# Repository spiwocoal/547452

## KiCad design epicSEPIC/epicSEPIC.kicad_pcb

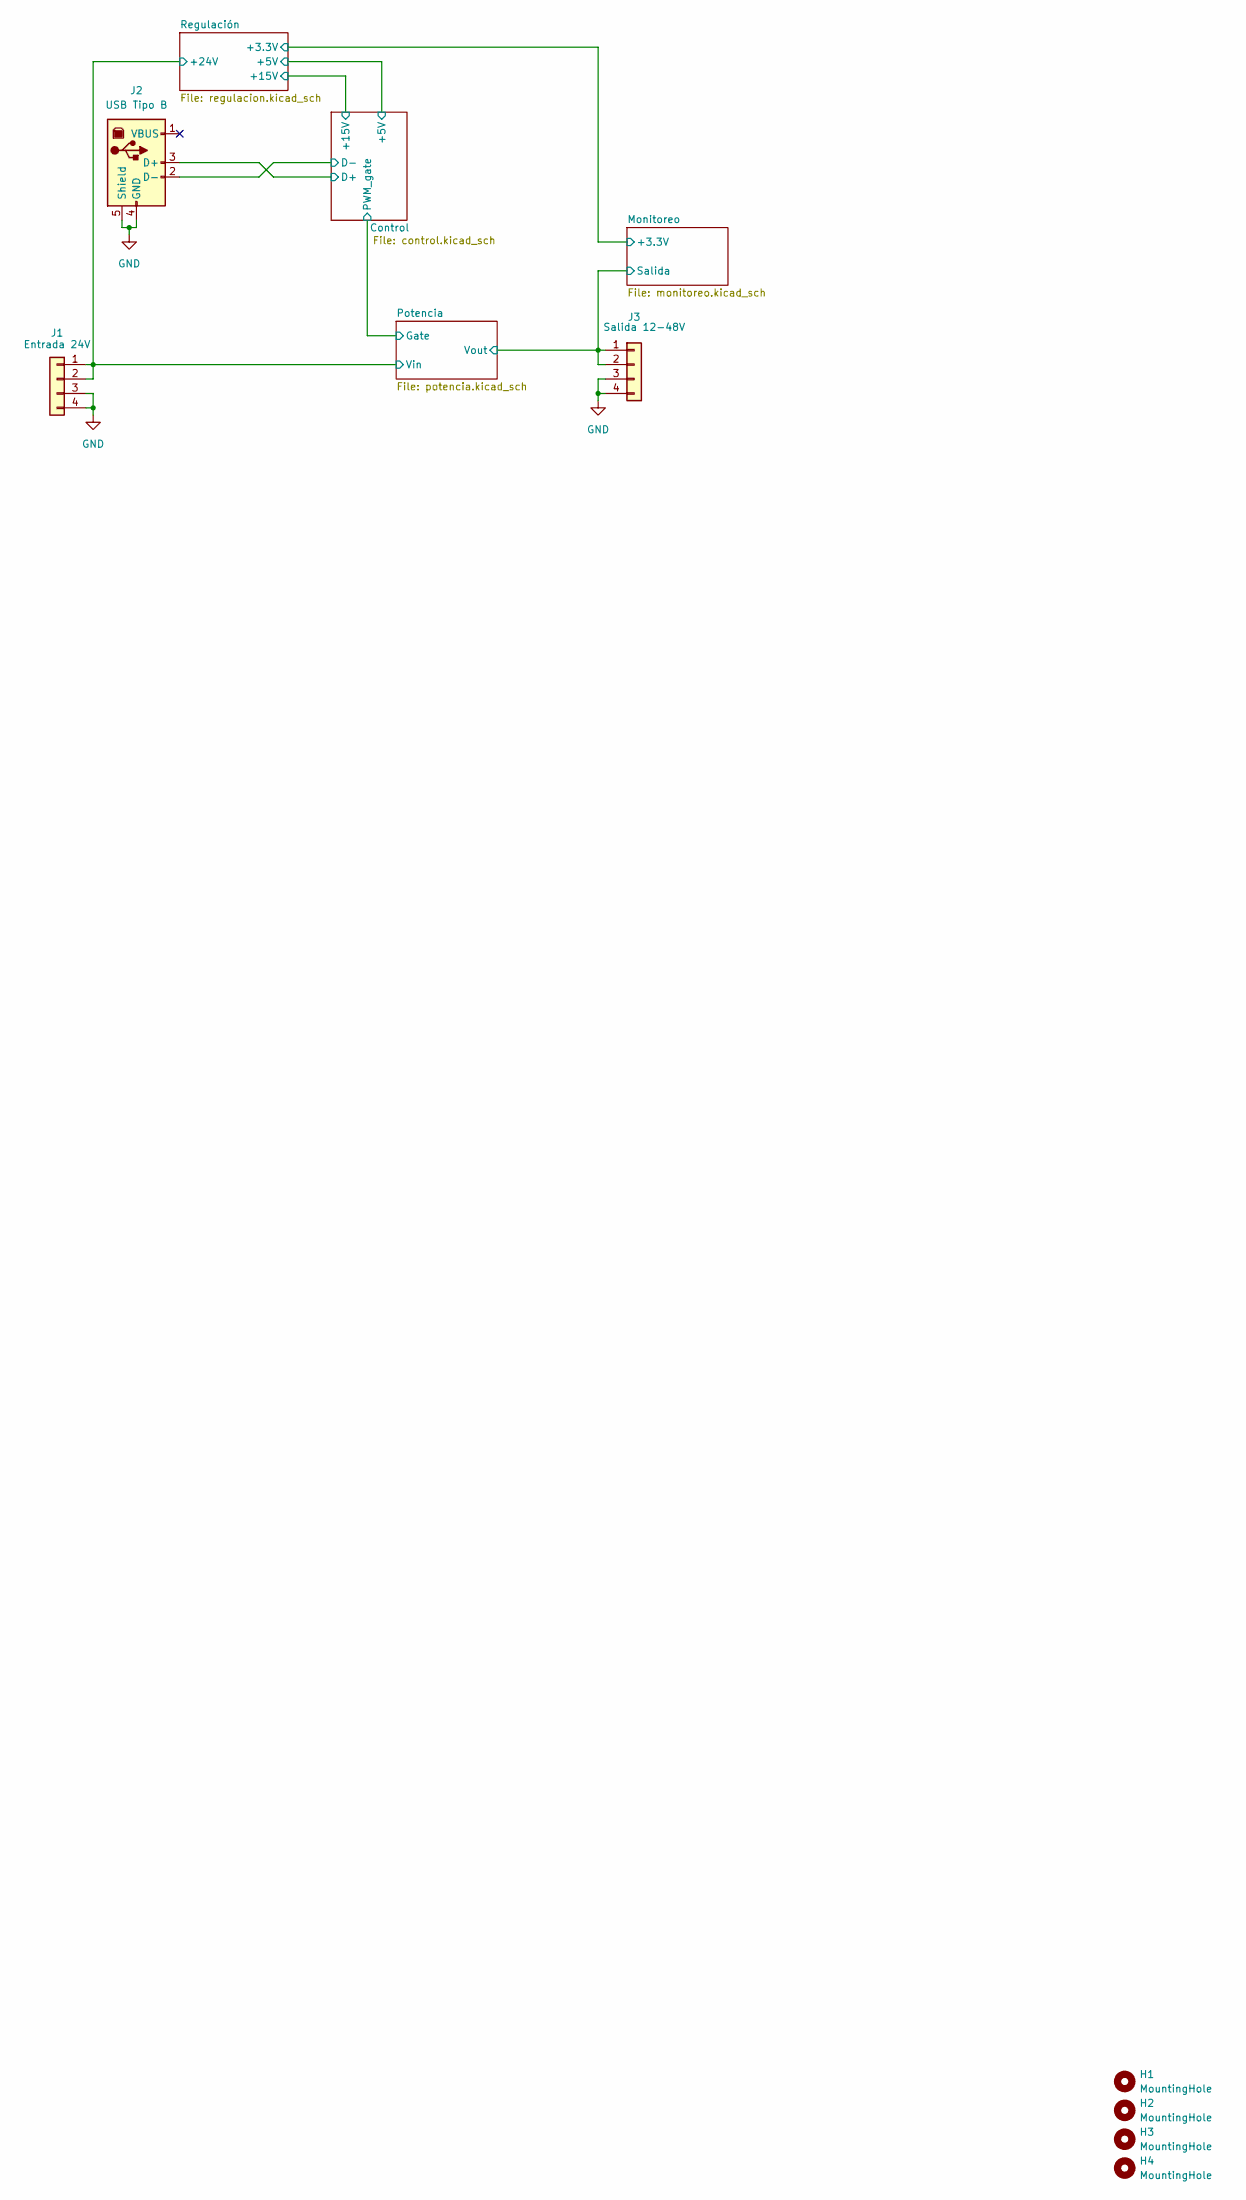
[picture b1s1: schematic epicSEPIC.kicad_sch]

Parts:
H1, H2, H3, H4: MountingHole; MountingHole_3.2mm_M3_ISO14580
J1: Entrada 24V; 1822752; MfgPN 1823638
J2: USB Tipo B; USB_B_Lumberg_2411_02_Horizontal; MfgPN 61729-0010RLF
J3: Salida 12-48V; 1822752; MfgPN 1823638

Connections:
/Control/D+: J2.3 (D+); also elsewhere on the board
/Control/D-: J2.2 (D-); also elsewhere on the board
/Monitoreo/Salida: J3.1, J3.2; also elsewhere on the board
/Potencia/Vin: J1.1, J1.2; also elsewhere on the board
GND: J1.3, J1.4, J2.4 (GND), J2.5 (Shield), J3.3, J3.4; also elsewhere on the board

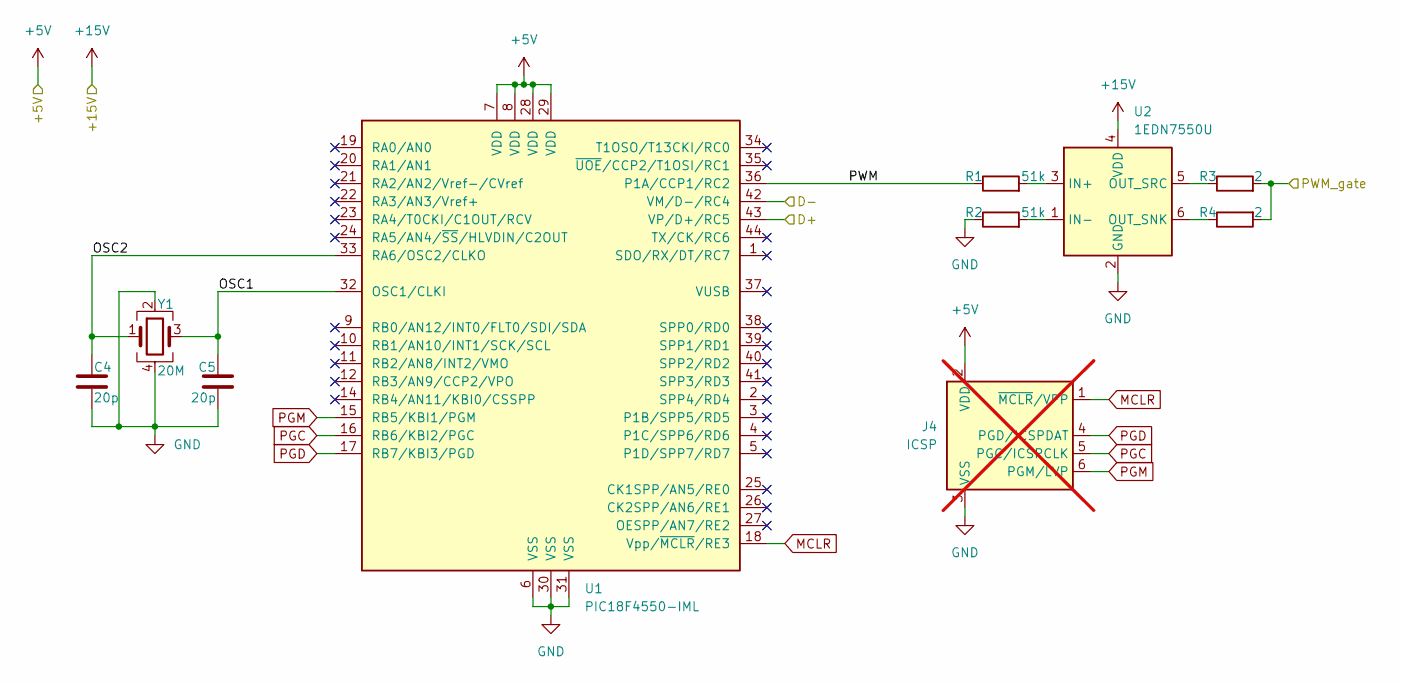
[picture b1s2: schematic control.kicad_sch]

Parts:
C4, C5: 20p; C_0402_1005Metric; MfgPN C0402C200M8HACTU
J4: ICSP; PinSocket_1x06_P1.00mm_Vertical; not fitted
R1, R2: 51k; R_0603_1608Metric; MfgPN ESR03EZPD5102
R3, R4: 2; R_0402_1005Metric; MfgPN RT0402BRE072RL
U1: PIC18F4550-IML; QFN-44-1EP_8x8mm_P0.65mm_EP6.45x6.45mm; MfgPN PIC18F4550-IML
U2: 1EDN7550U; PG-TSNP-6-13; MfgPN 1EDN7550U
Y1: 20M; Crystal_SMD_2520-4Pin_2.5x2.0mm; MfgPN FH2000021

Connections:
+5V: J4.2 (VDD), U1.7 (VDD), U1.8 (VDD), U1.28 (VDD), U1.29 (VDD); also elsewhere on the board
+15V: U2.4 (VDD); also elsewhere on the board
/Control/D+: U1.43 (VP/D+/RC5); also elsewhere on the board
/Control/D-: U1.42 (VM/D-/RC4); also elsewhere on the board
/Control/OSC1: C5.2, U1.32 (OSC1/CLKI), Y1.3
/Control/OSC2: C4.1, U1.33 (RA6/OSC2/CLKO), Y1.1
/Control/PWM: R1.1, U1.36 (P1A/CCP1/RC2)
/Control/PWM_gate: R3.2, R4.2; also elsewhere on the board
GND: C4.2, C5.1, J4.3 (VSS), R2.1, U1.6 (VSS), U1.30 (VSS), U1.31 (VSS), U2.2 (GND), Y1.2, Y1.4; also elsewhere on the board
MCLR: J4.1 (~MCLR/VPP), U1.18 (Vpp/~MCLR/RE3)
unnamed: R1.2, U2.3 (IN+)
unnamed: R2.2, U2.1 (IN-)
unnamed: R4.1, U2.6 (OUT_SNK)
unnamed: R3.1, U2.5 (OUT_SRC)
PGC: J4.5 (PGC/ICSPCLK), U1.16 (RB6/KBI2/PGC)
PGD: J4.4 (PGD/ICSPDAT), U1.17 (RB7/KBI3/PGD)
PGM: J4.6 (PGM/LVP), U1.15 (RB5/KBI1/PGM)

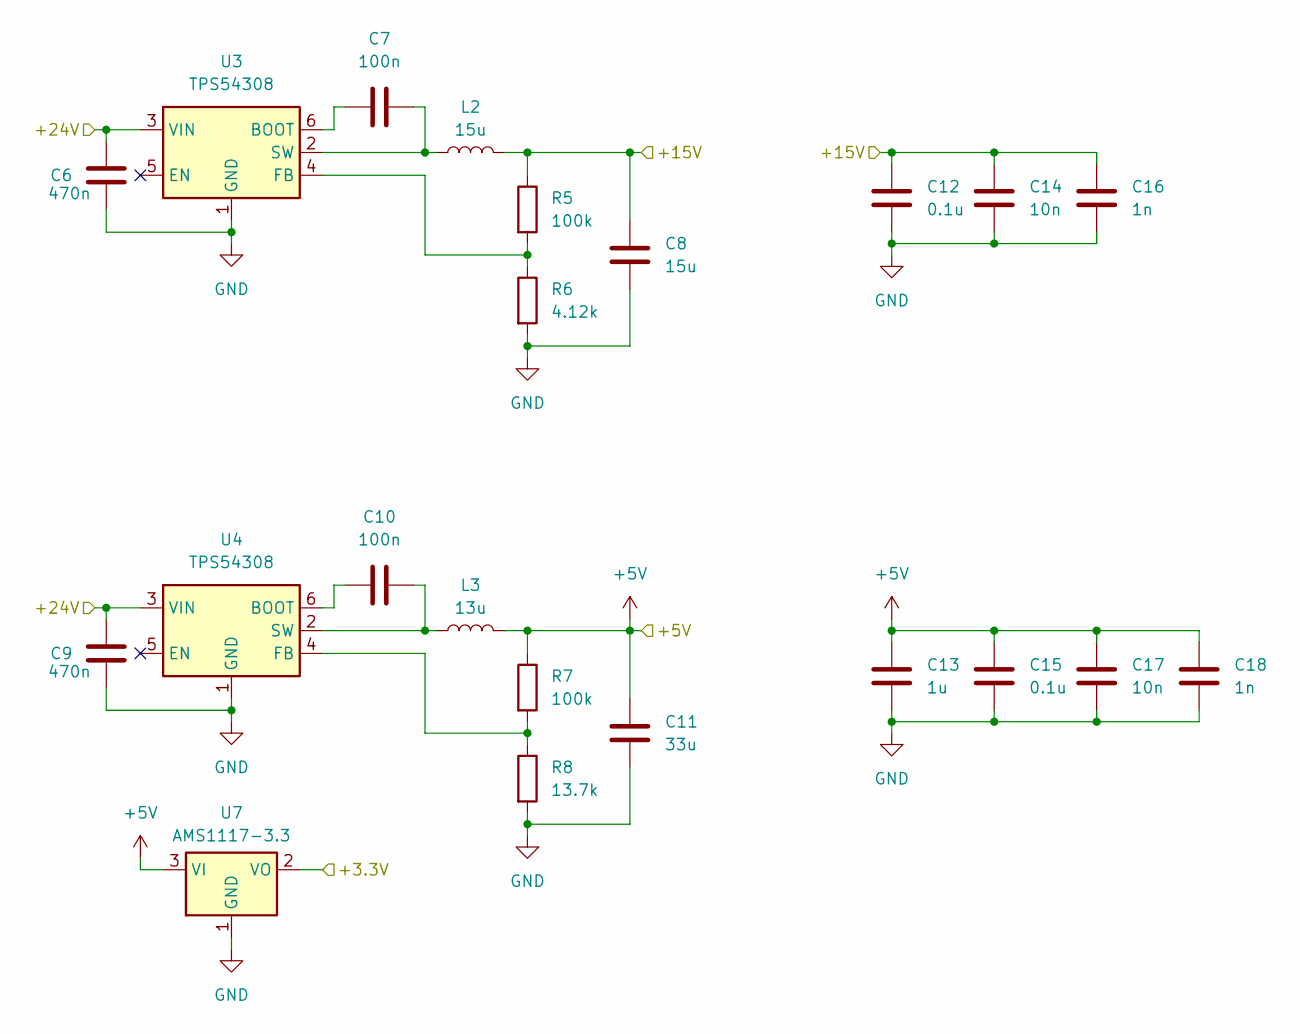
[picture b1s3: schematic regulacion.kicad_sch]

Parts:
C6, C9: 470n; C_0603_1608Metric; MfgPN CGA3E3X5R1V474K080AB
C7, C10: 100n; C_0402_1005Metric; MfgPN C1005X7R1H104K050BB
C8: 15u; C_0805_2012Metric; MfgPN C2012X5R1V156M125AC
C11: 33u; C_0805_2012Metric; MfgPN C2012X5R1A336M125AC
C12: 0.1u; C_0805_2012Metric; MfgPN C0805C104M4RACTU
C13: 1u; C_0805_2012Metric; MfgPN C0805C105M8RACTU
C14: 10n; C_0603_1608Metric; MfgPN C0603C103M4RACTU
C15: 0.1u; C_0805_2012Metric; MfgPN C0805C104M8RACTU
C16: 1n; C_0402_1005Metric; MfgPN C0402C102M4RACTU
C17: 10n; C_0603_1608Metric; MfgPN C0603C103M8RACTU
C18: 1n; C_0402_1005Metric; MfgPN C0402C102M8RACTU
L2: 15u; L_Wurth_WE-LHMI-7050; MfgPN 74437349150
L3: 13u; L_Wurth_WE-PDF-1064; MfgPN 7447798131
R5, R7: 100k; R_0402_1005Metric; MfgPN CRCW0402100KFKED
R6: 4.12k; R_0402_1005Metric; MfgPN CRCW04024K12FKED
R8: 13.7k; R_0402_1005Metric; MfgPN CRCW040213K7FKED
U3, U4: TPS54308; SOT-23-6; MfgPN TPS54308
U7: AMS1117-3.3; SOT-223-3_TabPin2

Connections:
+3.3V: U7.2 (VO); also elsewhere on the board
+5V: C11.2, C13.1, C15.1, C17.1, C18.1, L3.2, R7.1, U7.3 (VI); also elsewhere on the board
+15V: C8.2, C12.1, C14.1, C16.1, L2.2, R5.1; also elsewhere on the board
/Potencia/Vin: C6.1, C9.1, U3.3 (VIN), U4.3 (VIN); also elsewhere on the board
GND: C6.2, C8.1, C9.2, C11.1, C12.2, C13.2, C14.2, C15.2, C16.2, C17.2, C18.2, R6.2, R8.2, U3.1 (GND), U4.1 (GND), U7.1 (GND); also elsewhere on the board
unnamed: C7.1, U3.6 (BOOT)
unnamed: R5.2, R6.1, U3.4 (FB)
unnamed: C7.2, L2.1, U3.2 (SW)
unnamed: C10.1, U4.6 (BOOT)
unnamed: R7.2, R8.1, U4.4 (FB)
unnamed: C10.2, L3.1, U4.2 (SW)

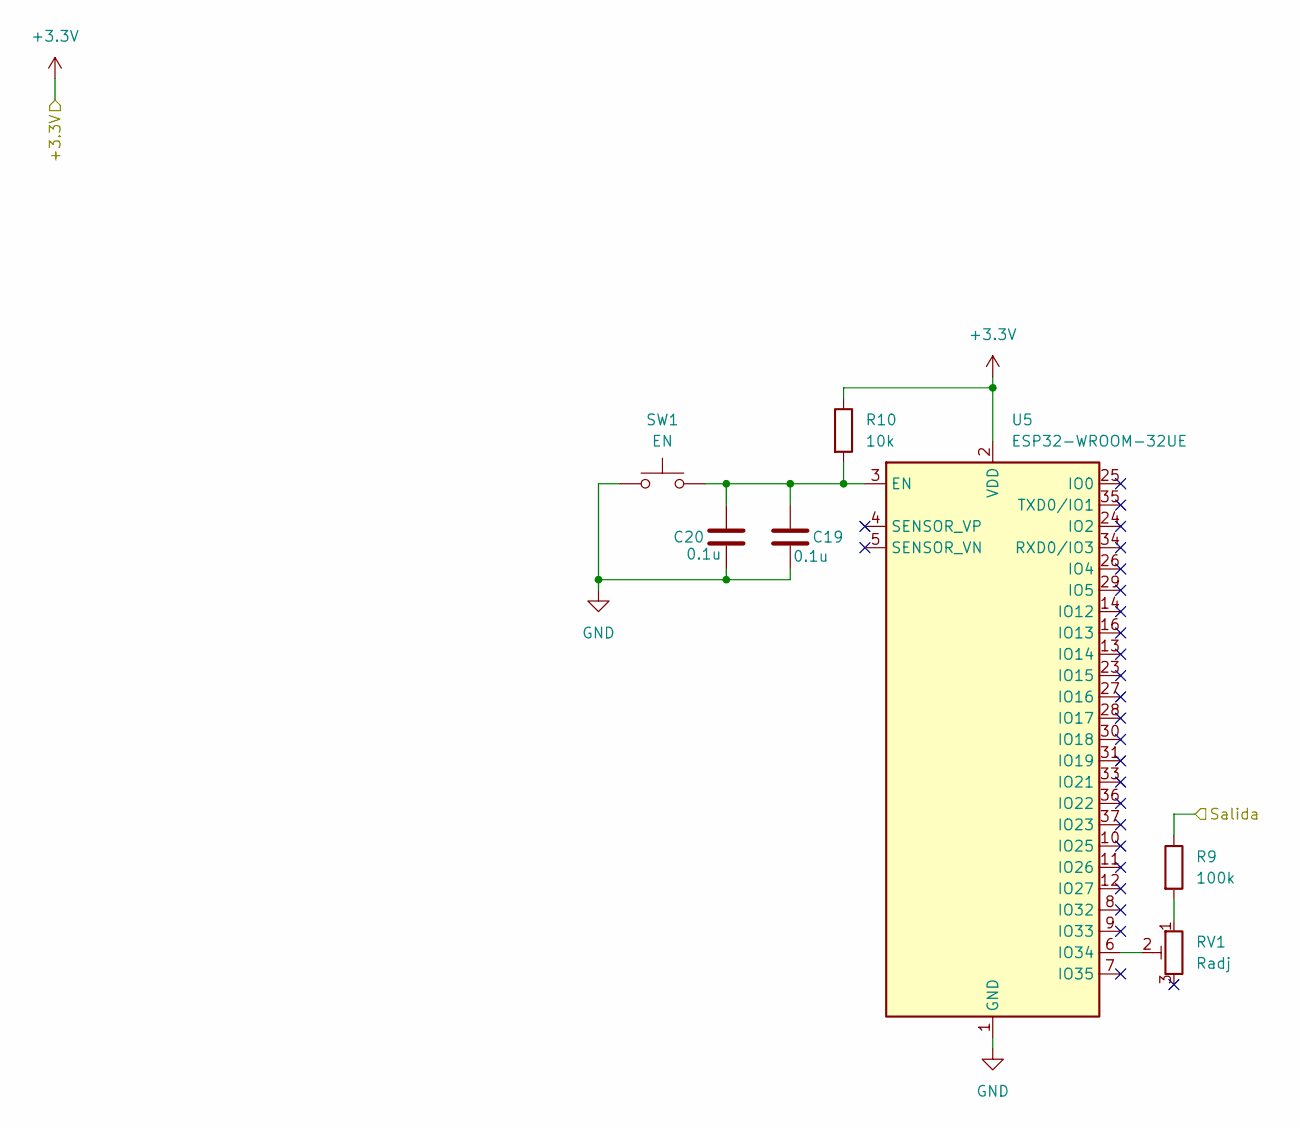
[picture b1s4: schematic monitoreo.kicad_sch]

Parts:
C19, C20: 0.1u; C_0201_0603Metric
R9: 100k; R_0201_0603Metric
R10: 10k; R_0201_0603Metric
RV1: Radj; 3313J1102E
SW1: EN; SW_SPST_B3U-1000P-B
U5: ESP32-WROOM-32UE

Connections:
+3.3V: R10.1, U5.2 (VDD); also elsewhere on the board
/Monitoreo/Salida: R9.1; also elsewhere on the board
GND: C19.2, C20.2, SW1.1, U5.1 (GND), U5.15 (GND), U5.38 (GND), U5.39 (GND); also elsewhere on the board
unnamed: R9.2, RV1.1
unnamed: C19.1, C20.1, R10.2, SW1.2, U5.3 (EN)
unnamed: RV1.2, U5.6 (IO34)

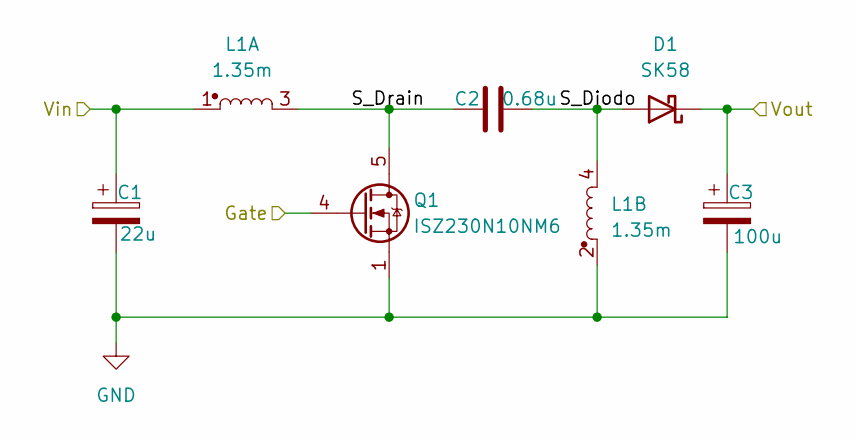
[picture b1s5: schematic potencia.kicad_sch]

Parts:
C1: 22u; CP_Elec_8x10; MfgPN A767KN226M1HLAE050
C2: 0.68u; C_1206_3216Metric; MfgPN C1206C684M1RACTU
C3: 100u; CP_Elec_10x12.5; MfgPN A767MU107M1JLAE28
D1: SK58; D_SMB; MfgPN SK58
L1: 1.35m; SRF1280680M; MfgPN SRF1280-680M
Q1: ISZ230N10NM6; PG-TSDSON-8-25; MfgPN ISZ230N10NM6ATMA1

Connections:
/Control/PWM_gate: Q1.4 (G); also elsewhere on the board
/Monitoreo/Salida: C3.1, D1.1 (K); also elsewhere on the board
/Potencia/S_Diodo: C2.2, D1.2 (A), L1.4
/Potencia/S_Drain: C2.1, L1.3, Q1.5 (D)
/Potencia/Vin: C1.1, L1.1; also elsewhere on the board
GND: C1.2, C3.2, L1.2, Q1.1 (S); also elsewhere on the board

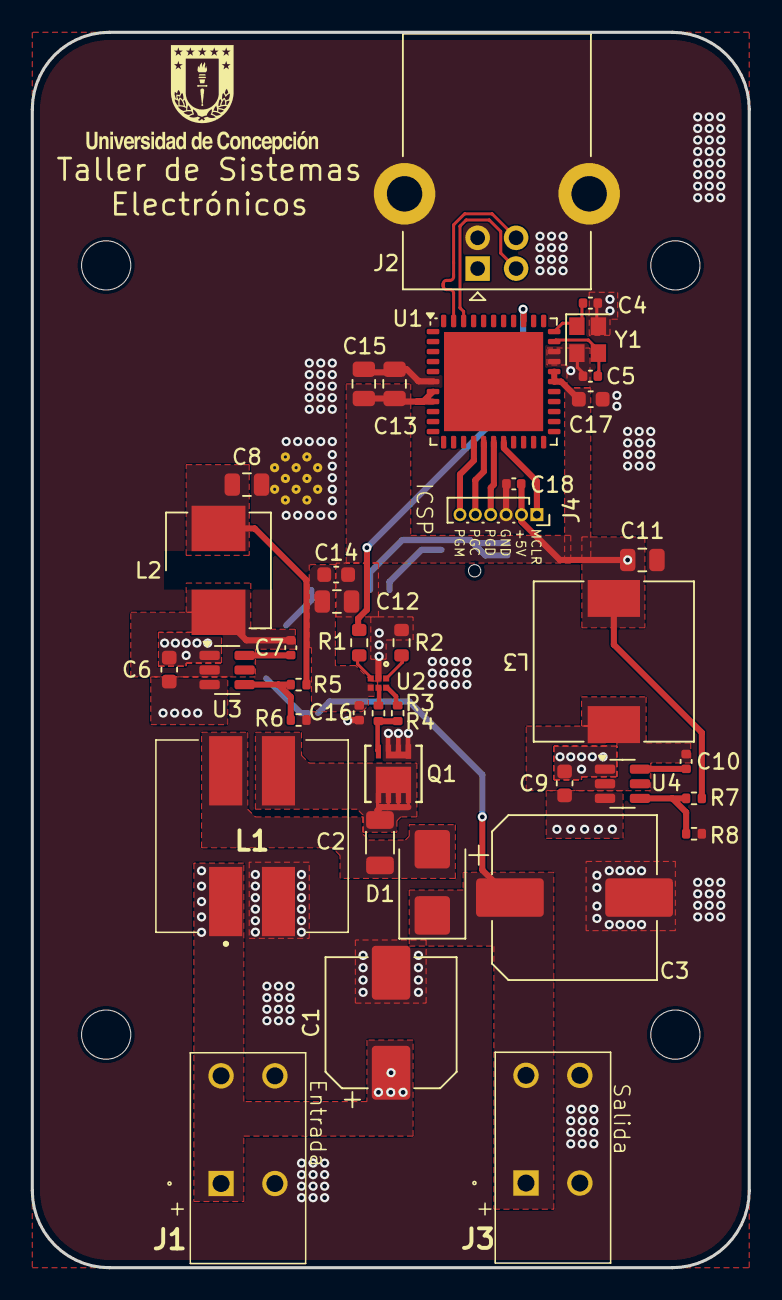
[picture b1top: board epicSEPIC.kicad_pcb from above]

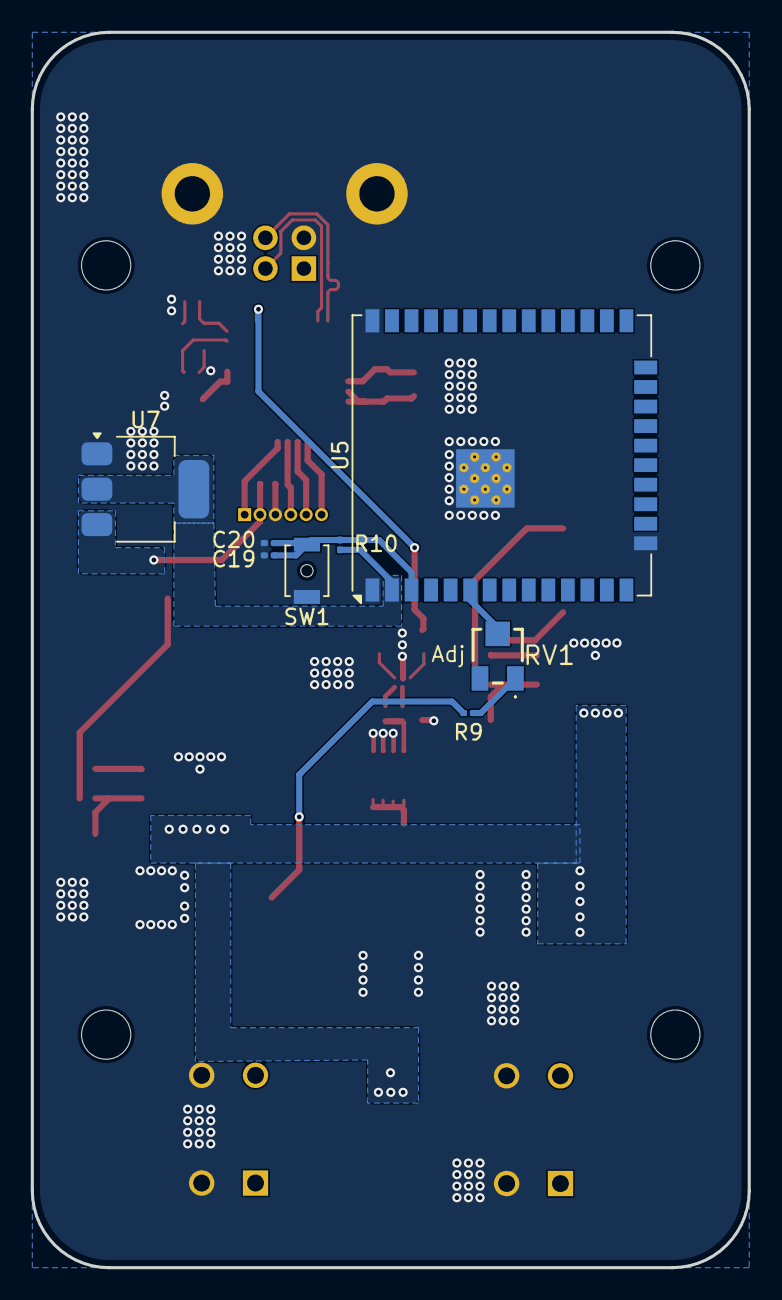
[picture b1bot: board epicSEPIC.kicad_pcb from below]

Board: 2 copper layers, 46.6 x 80.3 mm, 52 parts (8 on the bottom side), 31 nets.

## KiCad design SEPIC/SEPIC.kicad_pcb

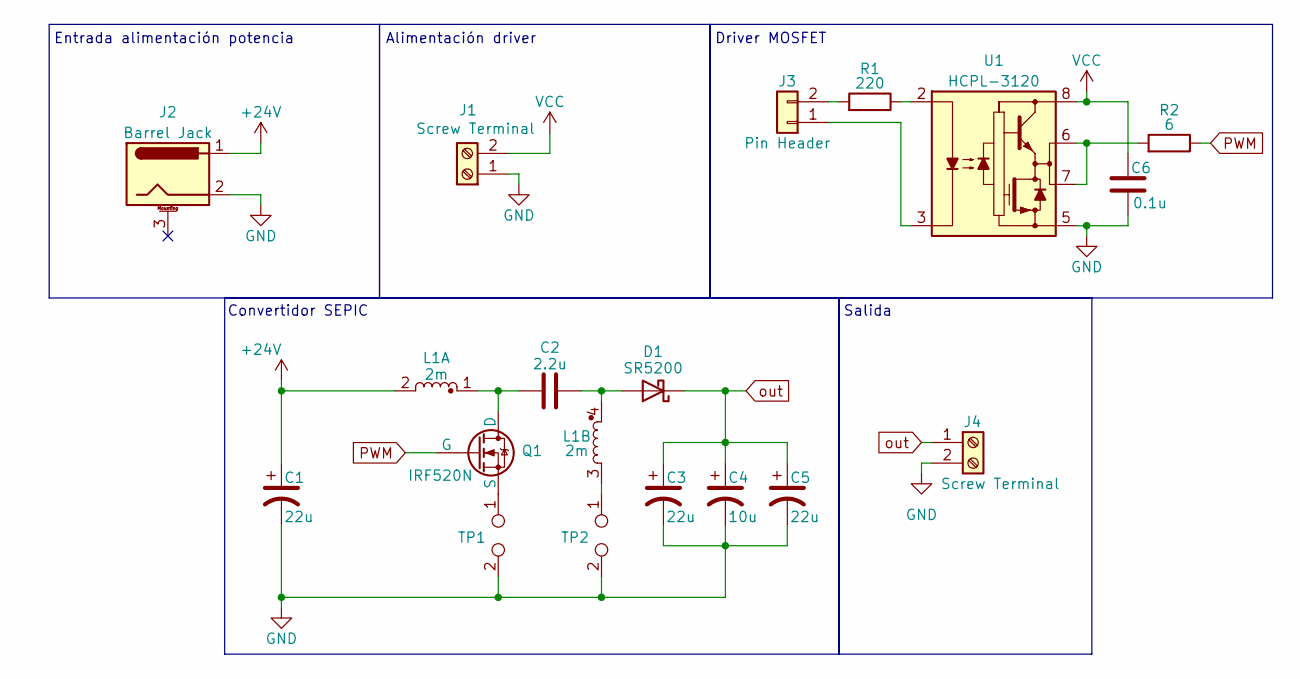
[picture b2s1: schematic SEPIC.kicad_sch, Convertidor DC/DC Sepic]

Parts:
C1: 22u; C_Radial_D10.0mm_H20.0mm_P5.00mm
C2: 2.2u; C_Rect_L16.5mm_W8.7mm_P15.00mm_MKT
C3, C5: 22u; C_Radial_D8.0mm_H11.5mm_P3.50mm
C4: 10u; C_Radial_D6.3mm_H7.0mm_P2.50mm
C6: 0.1u; C_Disc_D4.7mm_W2.5mm_P5.00mm
D1: SR5200; D_A-405_P7.62mm_Horizontal
J1, J4: Screw Terminal; TerminalBlock_Phoenix_MKDS-1,5-2-5.08_1x02_P5.08mm_Horizont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
J2: Barrel Jack; BarrelJack_Horizontal
J3: Pin Header; PinHeader_1x02_P2.54mm_Vertical
L1: 2m; L_CommonMode_Toroid_Vertical_L24.0mm_W16.3mm_Px10.16mm_Py20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
Q1: IRF520N; TO-220-3_Vertical
R1: 220; R_Axial_DIN0309_L9.0mm_D3.2mm_P2.54mm_Vertical
R2: 6; R_Axial_DIN0309_L9.0mm_D3.2mm_P12.70mm_Horizontal
TP1, TP2: Shunt; R_Axial_DIN0411_L9.9mm_D3.6mm_P25.40mm_Horizontal
U1: HCPL-3120; DIP-8_W7.62mm_Socket

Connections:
+24V: C1.1, J2.1, L1.2
GND: C1.2, C3.2, C4.2, C5.2, C6.2, J1.1, J2.2, J4.2, TP1.2, TP2.2, U1.5 (VEE)
unnamed: C2.2, D1.2 (A), L1.4
unnamed: J3.1, U1.3 (C)
unnamed: J3.2, R1.2
unnamed: L1.3, TP2.1
unnamed: C2.1, L1.1, Q1.2 (D)
unnamed: Q1.3 (S), TP1.1
unnamed: R2.2, U1.6 (VO), U1.7 (VO)
unnamed: R1.1, U1.2 (A)
PWM: Q1.1 (G), R2.1
VCC: C6.1, J1.2, U1.8 (VCC)
out: C3.1, C4.1, C5.1, D1.1 (K), J4.1

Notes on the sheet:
Driver MOSFET
Alimentación driver
Entrada alimentación potencia
Salida
Convertidor SEPIC

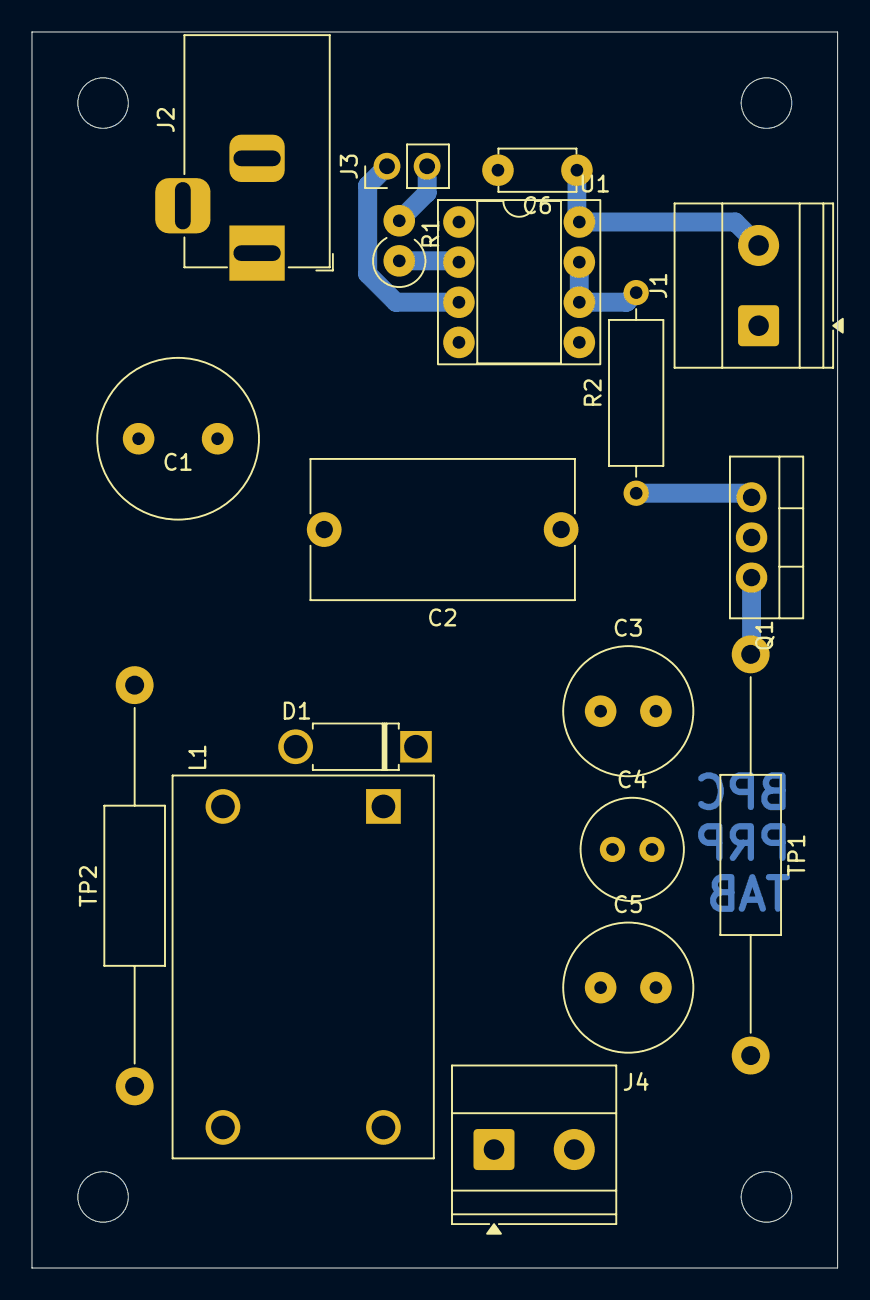
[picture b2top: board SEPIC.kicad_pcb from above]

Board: 2 copper layers, 51.0 x 78.2 mm, 18 parts (0 on the bottom side), 13 nets.

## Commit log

2025-08-28 Placa v0.1
2025-08-30 Diseño de PCB finalizado, generación de gerber
2025-08-30 Agregar referencias y datasheets
2025-08-31 Arreglar pines MOSFET
2025-09-01 Agregar graficos a PCB
2025-09-01 WIP: redimensionar componentes PCB
2025-09-02 PCB aprobada por Seba
2025-09-03 Agregar testpoints corriente PCB
2025-09-08 Agregar puntos medición corriente
2025-09-08 Simulacion SPICE
2025-09-09 Condensadores salida
2025-09-09 Simulacion con valores medidos
2025-09-11 Cambiar tamaño perforaciones
2025-09-11 Agregar carpeta para PIC
2025-09-11 Agregar datasheets PIC
2025-09-25 Carta Gantt actualizada
2025-09-25 Imagenes PCB
2025-10-09 Graficos variacion duty cycle
2025-10-09 Agregar proyecto MPLAB
2025-10-09 Agregar modelo 3D coil former
2025-10-19 Renombrar archivos ngspice
2025-10-20 WIP: PCB producto final
2025-10-24 PCB prototipo mejorado
2025-10-27 Agregar repo para GUI
2025-11-05 pic18: librería para pwm y adc
2025-11-16 Ordenar código nivel 2
2025-11-16 Actualizar carta gantt
2025-11-17 WIP: código PIC18 para interfaz mediante USB
2025-11-17 WIP: rampa duty cycle
2025-11-18 WIP: rampa duty cycle, tasa de refresco 1ms
2025-11-21 Arreglar tracking de archivos MPLAB con git
2025-11-24 Actualizar gui
2025-11-24 Arreglar proyecto MPLAB
2025-11-26 Esta wea no funciona v1
2025-11-26 Esta wea no funciona v2
2025-11-26 Comunicación serial funcionando
2025-11-27 Ahora si funciona esta wea
2025-11-27 Agregar proyecto de prueba pwm
2025-12-02 Arreglar rampa de duty
2025-12-02 Agregar plantilla para informe
2025-12-03 PCB Final en proceso, encontré el inductor
2025-12-04 Agregar repo submodulo para informe
2025-12-04 Diseño de PCB final
2025-12-04 PCB final
2025-12-04 Agregar datasheets
2025-12-07 PCB Final con reguladores
2025-12-09 Agregar video y fotos modelo 3D
2025-12-09 Actualizar BOM
2025-12-09 fixup! Actualizar BOM
2025-12-14 Conexión de interfaz gráfica con ESP-32
2025-12-15 Actualizar submodulos
2025-12-16 Agregar ESP32 a pcb
2025-12-16 ESP32 agregado
2025-12-18 Arreglar modelos 3D
2025-12-19 Actualizar informe, agregar guia usuario
